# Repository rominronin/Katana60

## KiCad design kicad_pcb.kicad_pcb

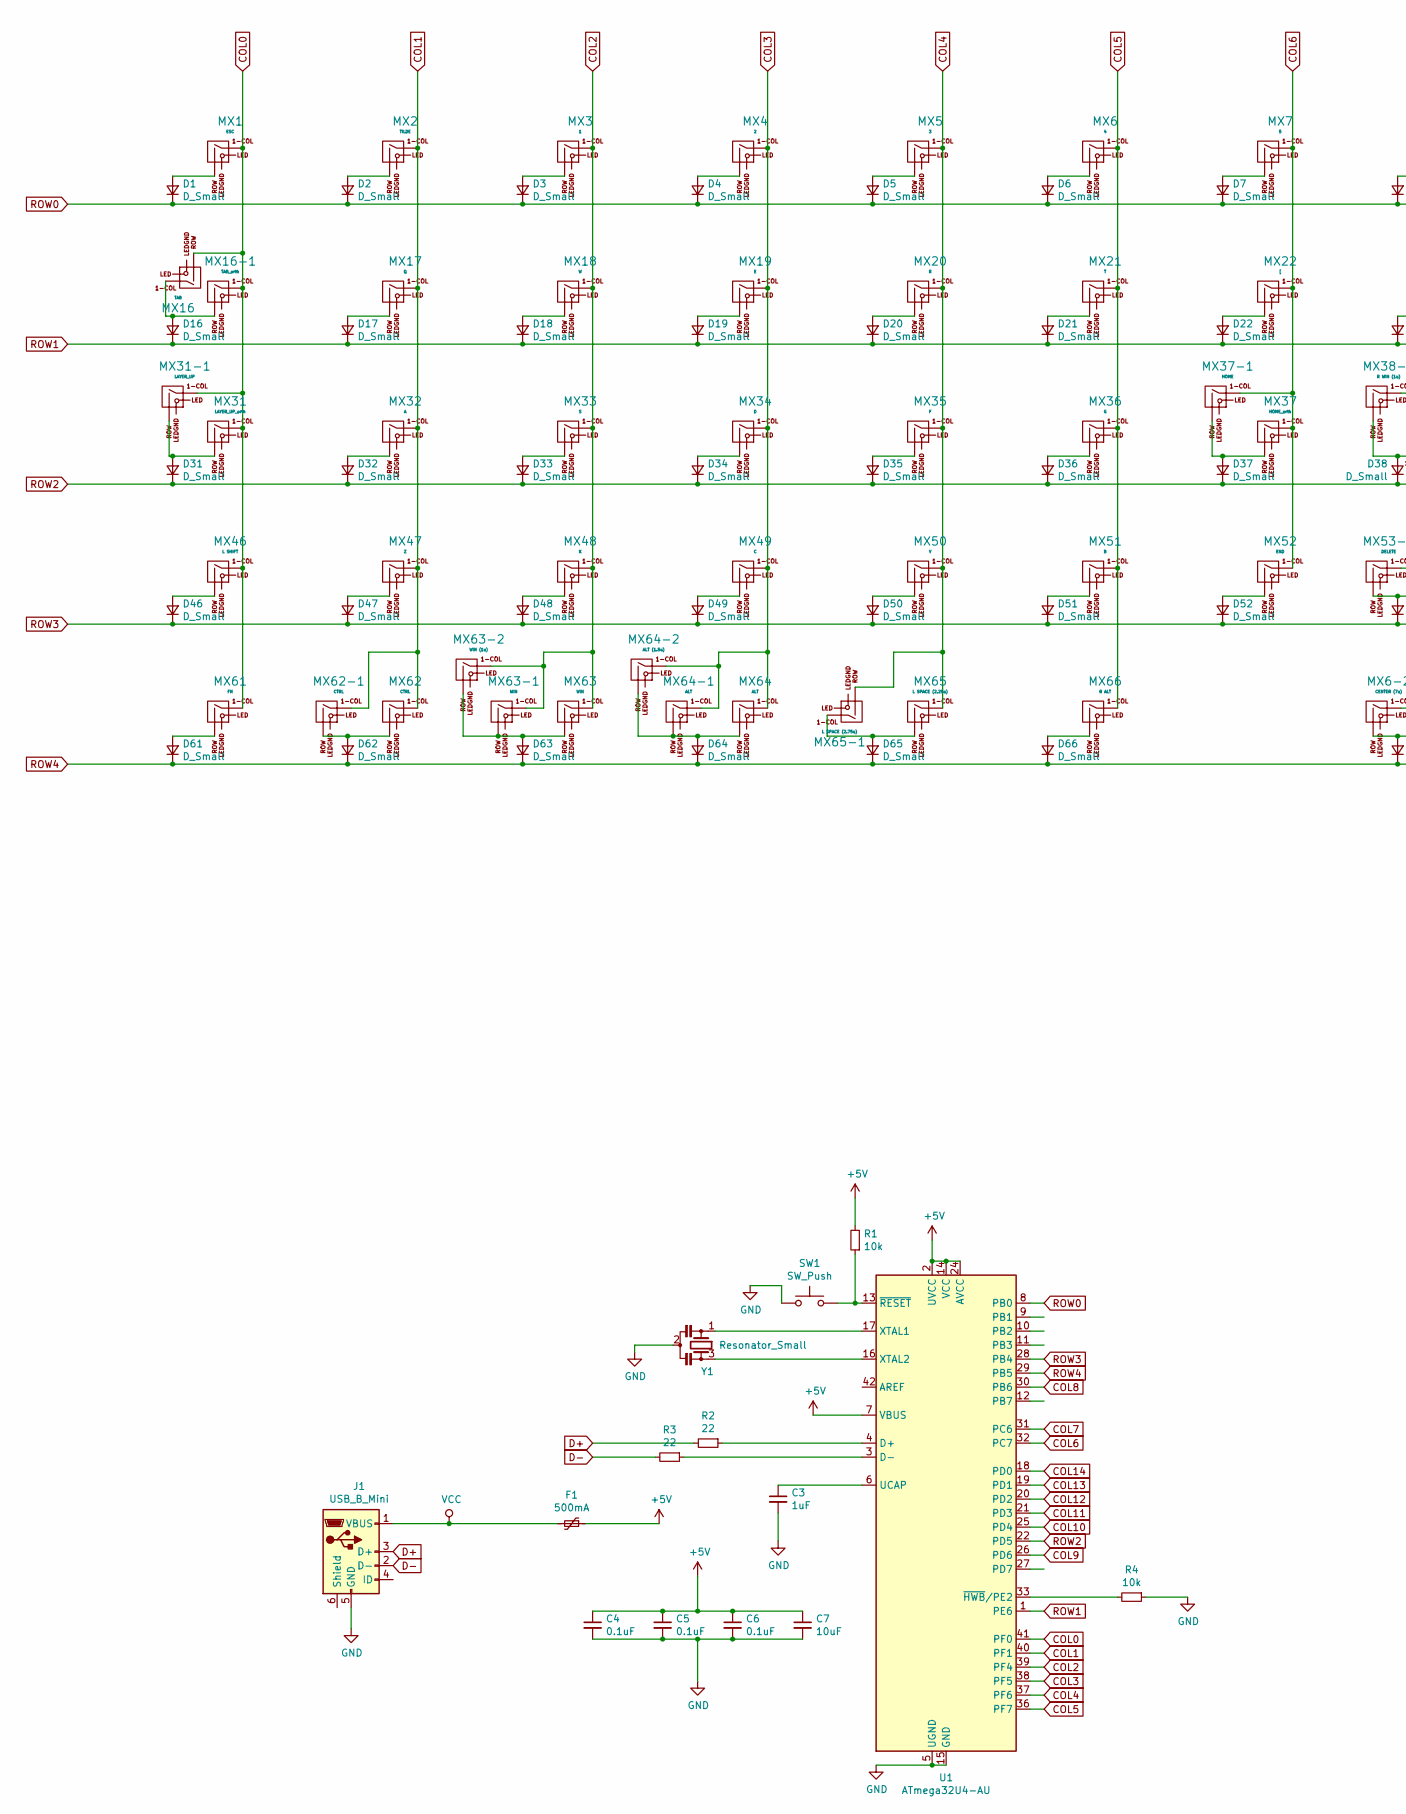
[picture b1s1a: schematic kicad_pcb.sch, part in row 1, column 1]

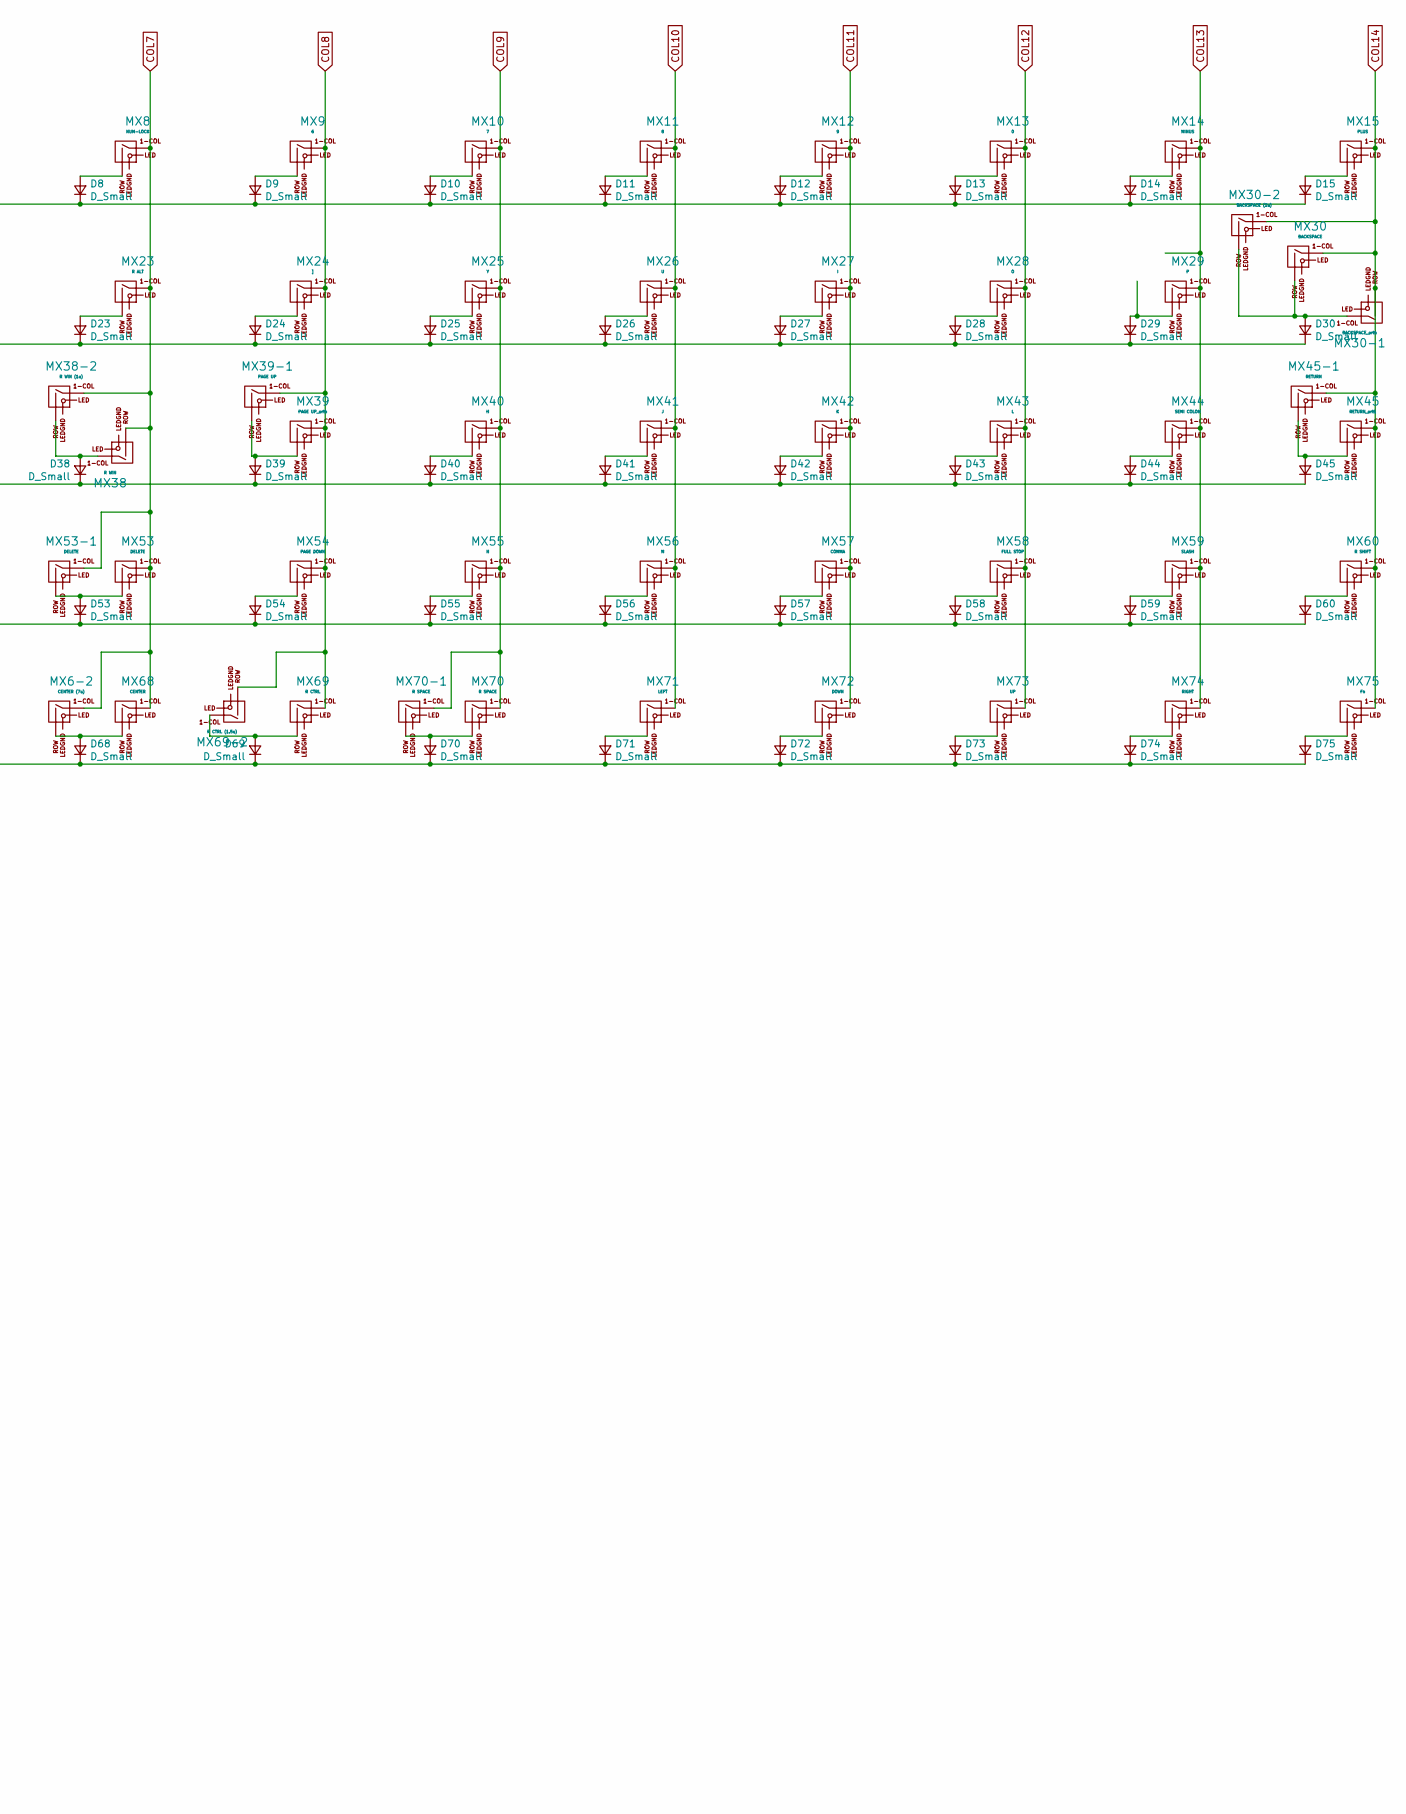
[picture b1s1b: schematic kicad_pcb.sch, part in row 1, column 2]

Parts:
C3: 1uF; C_0805_2012Metric
C4, C5, C6: 0.1uF; C_0805_2012Metric
C7: 10uF; D_0805_2012Metric
D1, D2, D3, D4, D5, D6, D7, D8, D9, D10, D11, D12, D13, D14, D15, D16, D17, D18, D19, D20, D21, D22, D23, D24, D25, D26, D27, D28, D29, D30, D31, D32, D33, D34, D35, D36, D37, D38, D39, D40, D41, D42, D43, D44, D45, D46, D47, D48, D49, D50, D51, D52, D53, D54, D55, D56, D57, D58, D59, D60, D61, D62, D63, D64, D65, D66, D68, D69, D70, D71, D72, D73, D74, D75: D_Small; D_0805_2012Metric
F1: 500mA; Fuse_1206_3216Metric
J1: USB_B_Mini; Molex-0548190519
MX1: ESC; MX-1U-NoLED
MX2: TILDE; MX-1U-NoLED
MX3: 1; MX-1U-NoLED
MX4: 2; MX-1U-NoLED
MX5: 3; MX-1U-NoLED
MX6: 4; MX-1U-NoLED
MX6-2: CENTER (7u); MX-7U-ReversedStabilizers-NoLED
MX7: 5; MX-1U-NoLED
MX8: NUM-LOCK; MX-1U-NoLED
MX9: 6; MX-1U-NoLED
MX10: 7; MX-1U-NoLED
MX11: 8; MX-1U-NoLED
MX12: 9; MX-1U-NoLED
MX13: 0; MX-1U-NoLED
MX14: MINUS; MX-1U-NoLED
MX15: PLUS; MX-1U-NoLED
MX16: TAB; MX-1.5U-NoLED
MX16-1: TAB_orth; MX-1U-NoLED
MX17: Q; MX-1U-NoLED
MX18: W; MX-1U-NoLED
MX19: E; MX-1U-NoLED
MX20: R; MX-1U-NoLED
MX21: T; MX-1U-NoLED
MX22: [; MX-1U-NoLED
MX23: R ALT; MX-2U-NoLED
MX24: ]; MX-1U-NoLED
MX25: Y; MX-1U-NoLED
MX26: U; MX-1U-NoLED
MX27: I; MX-1U-NoLED
MX28: O; MX-1U-NoLED
MX29: P; MX-1U-NoLED
MX30: BACKSPACE; MX-1.5U-NoLED
MX30-1: BACKSPACE_orth; MX-1U-NoLED
MX30-2: BACKSPACE (2u); MX-2U-NoLED
MX31: LAYER_UP_orth; MX-1U-NoLED
MX31-1: LAYER_UP; MX-1.25U-NoLED
MX32: A; MX-1U-NoLED
MX33: S; MX-1U-NoLED
MX34: D; MX-1U-NoLED
MX35: F; MX-1U-NoLED
MX36: G; MX-1U-NoLED
MX37: HOME_orth; MX-1U-NoLED
MX37-1: HOME; MX-1.25U-NoLED
MX38: R WIN; MX-1.25U-NoLED
MX38-2: R WIN (1u); MX-1U-NoLED
MX39: PAGE UP_orth; MX-1U-NoLED
MX39-1: PAGE UP; MX-1.25U-NoLED
MX40: H; MX-1U-NoLED
MX41: J; MX-1U-NoLED
MX42: K; MX-1U-NoLED
MX43: L; MX-1U-NoLED
MX44: SEMI COLON; MX-1U-NoLED
MX45: RETURN_orth; MX-1U-NoLED
MX45-1: RETURN; MX-1.25U-NoLED
MX46: L SHIFT; MX-1U-NoLED
MX47: Z; MX-1U-NoLED
MX48: X; MX-1U-NoLED
MX49: C; MX-1U-NoLED
MX50: V; MX-1U-NoLED
MX51: B; MX-1U-NoLED
MX52: END; MX-1U-NoLED
MX53: DELETE; MX-1U-NoLED
MX53-1: DELETE; MX-2.75U-ReversedStabilizers-NoLED
MX54: PAGE DOWN; MX-1U-NoLED
MX55: N; MX-1U-NoLED
MX56: M; MX-1U-NoLED
MX57: COMMA; MX-1U-NoLED
MX58: FULL STOP; MX-1U-NoLED
MX59: SLASH; MX-1U-NoLED
MX60: R SHIFT; MX-1U-NoLED
MX61: FN; MX-1U-NoLED
MX62: CTRL; MX-1.25U-NoLED
MX62-1: CTRL; MX-1.5U-NoLED
MX63, MX63-1: WIN; MX-1.25U-NoLED
MX63-2: WIN (1u); MX-1U-NoLED
MX64: ALT; MX-1.25U-NoLED
MX64-1: ALT; MX-1.5U-NoLED
MX64-2: ALT (1.5u); MX-1.5U-NoLED
MX65: L SPACE (2.25u); MX-2.25U-ReversedStabilizers-NoLED
MX65-1: L SPACE (2.75u); MX-2.75U-NoLED
MX66: R ALT; MX-1.5U-NoLED
MX68: CENTER; MX-1U-NoLED
MX69: R CTRL; MX-2.25U-NoLED
MX69-2: R CTRL (1.5u); MX-1.5U-NoLED
MX70: R SPACE; MX-2U-ReversedStabilizers-NoLED
MX70-1: R SPACE; MX-2.75U-NoLED
MX71: LEFT; MX-1U-NoLED
MX72: DOWN; MX-1U-NoLED
MX73: UP; MX-1U-NoLED
MX74: RIGHT; MX-1U-NoLED
MX75: Fn; MX-1U-NoLED
R1, R4: 10k; R_0805_2012Metric
R2, R3: 22; R_0805_2012Metric
SW1: SW_Push; SKQG-1155865
U1: ATmega32U4-AU; TQFP-44_10x10mm_P0.8mm
Y1: Resonator_Small; Resonator_SMD_muRata_CSTxExxV-3Pin_3.0x1.1mm

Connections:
+5V: C4.1, C5.1, C6.1, C7.1, F1.1, R1.2, U1.2 (UVCC), U1.7 (VBUS), U1.14 (VCC), U1.24 (AVCC), U1.34 (VCC), U1.44 (AVCC)
COL0: MX1.1 (COL), MX16.2 (ROW), MX16-1.1 (COL), MX31.1 (COL), MX31-1.1 (COL), MX46.1 (COL), MX61.1 (COL), U1.41 (PF0)
COL1: MX2.1 (COL), MX17.1 (COL), MX32.1 (COL), MX47.1 (COL), MX62.1 (COL), MX62-1.1 (COL), U1.40 (PF1)
COL2: MX3.1 (COL), MX18.1 (COL), MX33.1 (COL), MX48.1 (COL), MX63.1 (COL), MX63-1.1 (COL), MX63-2.1 (COL), U1.39 (PF4)
COL3: MX4.1 (COL), MX19.1 (COL), MX34.1 (COL), MX49.1 (COL), MX64.1 (COL), MX64-1.1 (COL), MX64-2.1 (COL), U1.38 (PF5)
COL4: MX5.1 (COL), MX20.1 (COL), MX35.1 (COL), MX50.1 (COL), MX65.1 (COL), MX65-1.2 (ROW), U1.37 (PF6)
COL5: MX6.1 (COL), MX21.1 (COL), MX36.1 (COL), MX51.1 (COL), MX66.1 (COL), U1.36 (PF7)
COL6: MX7.1 (COL), MX22.1 (COL), MX37.1 (COL), MX37-1.1 (COL), MX52.1 (COL), U1.32 (PC7)
COL7: MX6-2.1 (COL), MX8.1 (COL), MX23.1 (COL), MX38.2 (ROW), MX38-2.1 (COL), MX53.1 (COL), MX53-1.1 (COL), MX68.1 (COL), U1.31 (PC6)
COL8: MX9.1 (COL), MX24.1 (COL), MX39.1 (COL), MX39-1.1 (COL), MX54.1 (COL), MX69.1 (COL), MX69-2.2 (ROW), U1.30 (PB6)
COL9: MX10.1 (COL), MX25.1 (COL), MX40.1 (COL), MX55.1 (COL), MX70.1 (COL), MX70-1.1 (COL), U1.26 (PD6)
COL10: MX11.1 (COL), MX26.1 (COL), MX41.1 (COL), MX56.1 (COL), MX71.1 (COL), U1.25 (PD4)
COL11: MX12.1 (COL), MX27.1 (COL), MX42.1 (COL), MX57.1 (COL), MX72.1 (COL), U1.21 (PD3)
COL12: MX13.1 (COL), MX28.1 (COL), MX43.1 (COL), MX58.1 (COL), MX73.1 (COL), U1.20 (PD2)
COL13: MX14.1 (COL), MX29.1 (COL), MX44.1 (COL), MX59.1 (COL), MX74.1 (COL), U1.19 (PD1)
COL14: MX15.1 (COL), MX30.1 (COL), MX30-1.2 (ROW), MX30-2.1 (COL), MX45.1 (COL), MX45-1.1 (COL), MX60.1 (COL), MX75.1 (COL), U1.18 (PD0)
D+: J1.3 (D+), R2.2
D-: J1.2 (D-), R3.2
GND: C3.2, C4.2, C5.2, C6.2, C7.2, J1.5 (GND), R4.1, SW1.1, U1.5 (UGND), U1.15 (GND), U1.23 (GND), U1.35 (GND), U1.43 (GND), Y1.2
unnamed: C3.1, U1.6 (UCAP)
unnamed: D1.2 (A), MX1.2 (ROW)
unnamed: D2.2 (A), MX2.2 (ROW)
unnamed: D3.2 (A), MX3.2 (ROW)
unnamed: D4.2 (A), MX4.2 (ROW)
unnamed: D5.2 (A), MX5.2 (ROW)
unnamed: D6.2 (A), MX6.2 (ROW)
unnamed: D7.2 (A), MX7.2 (ROW)
unnamed: D8.2 (A), MX8.2 (ROW)
unnamed: D9.2 (A), MX9.2 (ROW)
unnamed: D10.2 (A), MX10.2 (ROW)
unnamed: D11.2 (A), MX11.2 (ROW)
unnamed: D12.2 (A), MX12.2 (ROW)
unnamed: D13.2 (A), MX13.2 (ROW)
unnamed: D14.2 (A), MX14.2 (ROW)
unnamed: D15.2 (A), MX15.2 (ROW)
unnamed: D16.2 (A), MX16.1 (COL), MX16-1.2 (ROW)
unnamed: D17.2 (A), MX17.2 (ROW)
unnamed: D18.2 (A), MX18.2 (ROW)
unnamed: D19.2 (A), MX19.2 (ROW)
unnamed: D20.2 (A), MX20.2 (ROW)
unnamed: D21.2 (A), MX21.2 (ROW)
unnamed: D22.2 (A), MX22.2 (ROW)
unnamed: D23.2 (A), MX23.2 (ROW)
unnamed: D24.2 (A), MX24.2 (ROW)
unnamed: D25.2 (A), MX25.2 (ROW)
unnamed: D26.2 (A), MX26.2 (ROW)
unnamed: D27.2 (A), MX27.2 (ROW)
unnamed: D28.2 (A), MX28.2 (ROW)
unnamed: D29.2 (A), MX29.2 (ROW)
unnamed: D30.2 (A), MX30.2 (ROW), MX30-1.1 (COL), MX30-2.2 (ROW)
unnamed: D31.2 (A), MX31.2 (ROW), MX31-1.2 (ROW)
unnamed: D32.2 (A), MX32.2 (ROW)
unnamed: D33.2 (A), MX33.2 (ROW)
unnamed: D34.2 (A), MX34.2 (ROW)
unnamed: D35.2 (A), MX35.2 (ROW)
unnamed: D36.2 (A), MX36.2 (ROW)
unnamed: D37.2 (A), MX37.2 (ROW), MX37-1.2 (ROW)
unnamed: D38.2 (A), MX38.1 (COL), MX38-2.2 (ROW)
unnamed: D39.2 (A), MX39.2 (ROW), MX39-1.2 (ROW)
unnamed: D40.2 (A), MX40.2 (ROW)
unnamed: D41.2 (A), MX41.2 (ROW)
unnamed: D42.2 (A), MX42.2 (ROW)
unnamed: D43.2 (A), MX43.2 (ROW)
unnamed: D44.2 (A), MX44.2 (ROW)
unnamed: D45.2 (A), MX45.2 (ROW), MX45-1.2 (ROW)
unnamed: D46.2 (A), MX46.2 (ROW)
unnamed: D47.2 (A), MX47.2 (ROW)
unnamed: D48.2 (A), MX48.2 (ROW)
unnamed: D49.2 (A), MX49.2 (ROW)
unnamed: D50.2 (A), MX50.2 (ROW)
unnamed: D51.2 (A), MX51.2 (ROW)
unnamed: D52.2 (A), MX52.2 (ROW)
unnamed: D53.2 (A), MX53.2 (ROW), MX53-1.2 (ROW)
unnamed: D54.2 (A), MX54.2 (ROW)
unnamed: D55.2 (A), MX55.2 (ROW)
unnamed: D56.2 (A), MX56.2 (ROW)
unnamed: D57.2 (A), MX57.2 (ROW)
unnamed: D58.2 (A), MX58.2 (ROW)
unnamed: D59.2 (A), MX59.2 (ROW)
unnamed: D60.2 (A), MX60.2 (ROW)
unnamed: D61.2 (A), MX61.2 (ROW)
unnamed: D62.2 (A), MX62.2 (ROW), MX62-1.2 (ROW)
unnamed: D63.2 (A), MX63.2 (ROW), MX63-1.2 (ROW), MX63-2.2 (ROW)
unnamed: D64.2 (A), MX64.2 (ROW), MX64-1.2 (ROW), MX64-2.2 (ROW)
unnamed: D65.2 (A), MX65.2 (ROW), MX65-1.1 (COL)
unnamed: D66.2 (A), MX66.2 (ROW)
unnamed: D68.2 (A), MX6-2.2 (ROW), MX68.2 (ROW)
unnamed: D69.2 (A), MX69.2 (ROW), MX69-2.1 (COL)
unnamed: D70.2 (A), MX70.2 (ROW), MX70-1.2 (ROW)
unnamed: D71.2 (A), MX71.2 (ROW)
unnamed: D72.2 (A), MX72.2 (ROW)
unnamed: D73.2 (A), MX73.2 (ROW)
unnamed: D74.2 (A), MX74.2 (ROW)
unnamed: D75.2 (A), MX75.2 (ROW)
unnamed: R1.1, SW1.2, U1.13 (~RESET)
unnamed: R2.1, U1.4 (D+)
unnamed: R3.1, U1.3 (D-)
unnamed: R4.2, U1.33 (~HWB~/PE2)
unnamed: U1.16 (XTAL2), Y1.3
unnamed: U1.17 (XTAL1), Y1.1
ROW0: D1.1 (K), D2.1 (K), D3.1 (K), D4.1 (K), D5.1 (K), D6.1 (K), D7.1 (K), D8.1 (K), D9.1 (K), D10.1 (K), D11.1 (K), D12.1 (K), D13.1 (K), D14.1 (K), D15.1 (K), U1.8 (PB0)
ROW1: D16.1 (K), D17.1 (K), D18.1 (K), D19.1 (K), D20.1 (K), D21.1 (K), D22.1 (K), D23.1 (K), D24.1 (K), D25.1 (K), D26.1 (K), D27.1 (K), D28.1 (K), D29.1 (K), D30.1 (K), U1.1 (PE6)
ROW2: D31.1 (K), D32.1 (K), D33.1 (K), D34.1 (K), D35.1 (K), D36.1 (K), D37.1 (K), D38.1 (K), D39.1 (K), D40.1 (K), D41.1 (K), D42.1 (K), D43.1 (K), D44.1 (K), D45.1 (K), U1.22 (PD5)
ROW3: D46.1 (K), D47.1 (K), D48.1 (K), D49.1 (K), D50.1 (K), D51.1 (K), D52.1 (K), D53.1 (K), D54.1 (K), D55.1 (K), D56.1 (K), D57.1 (K), D58.1 (K), D59.1 (K), D60.1 (K), U1.28 (PB4)
ROW4: D61.1 (K), D62.1 (K), D63.1 (K), D64.1 (K), D65.1 (K), D66.1 (K), D68.1 (K), D69.1 (K), D70.1 (K), D71.1 (K), D72.1 (K), D73.1 (K), D74.1 (K), D75.1 (K), U1.29 (PB5)
VCC: F1.2, J1.1 (VBUS)

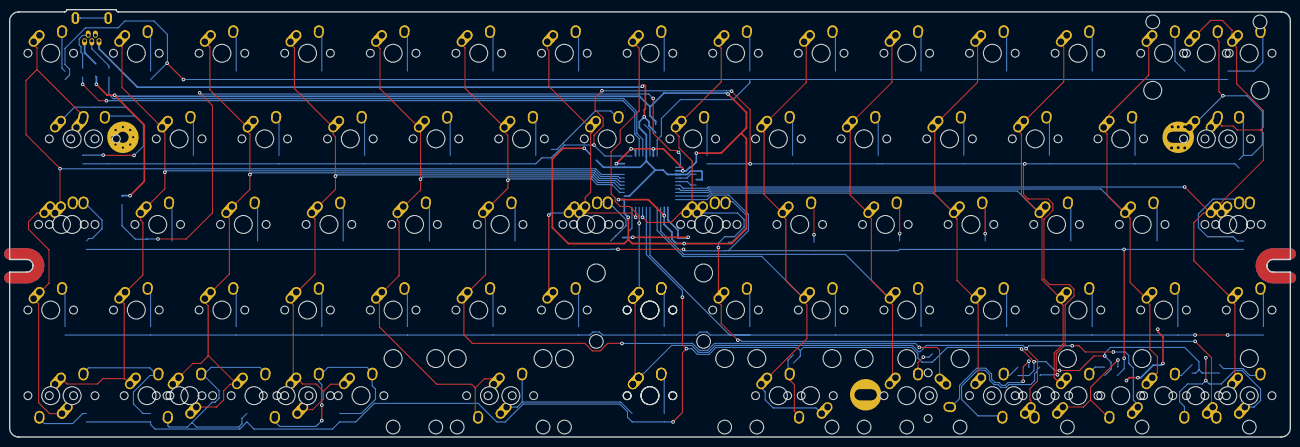
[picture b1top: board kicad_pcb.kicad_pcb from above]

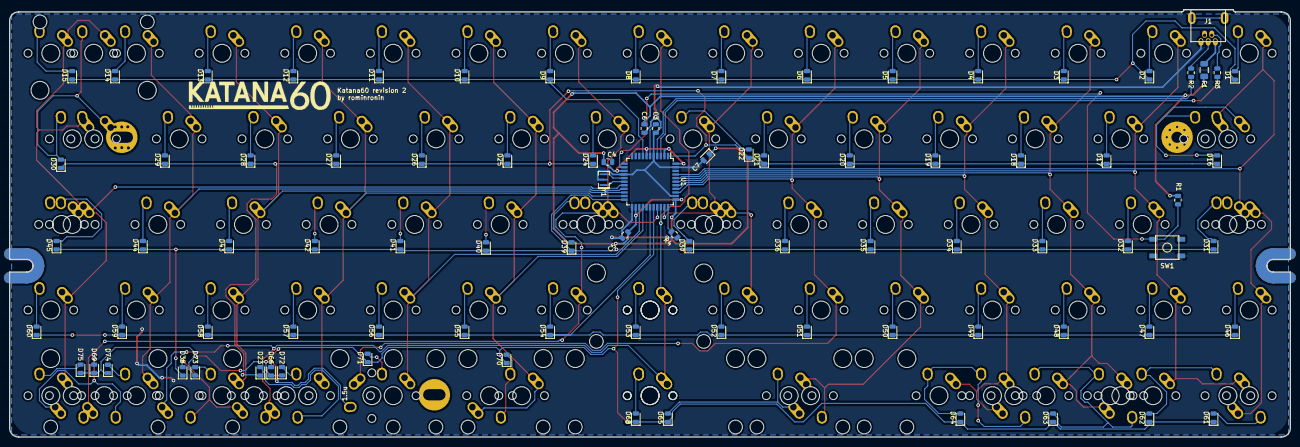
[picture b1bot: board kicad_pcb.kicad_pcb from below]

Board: 2 copper layers, 285.0 x 95.1 mm, 180 parts (88 on the bottom side), 106 nets.

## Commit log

2019-06-24 Ordered all keyboard rows
2019-06-24 Renamed all footprints except bottom row
2019-06-24 placed all the diodes
2019-07-02 updated the controller package
2019-07-02 latest changes
2019-07-02 flipped each component to the correct side, placed everything
2019-07-04 started with traces.
2019-07-04 further tracing
2019-07-05 further tracing applied
2019-07-06 first draft of the v2 PCB completed
2019-07-07 error-free first version
2019-07-07 ready to export
2019-07-07 updated the PCB outline footprint
2019-07-07 first export
2019-07-07 drill files added
2019-07-07 description
2019-07-07 updated the gerbers
2019-07-07 Added Katana60 logo to gerbers
2019-07-22 Gerber zip file
2019-07-26 ammended some incorrect footprints
2019-07-28 Moved and re-routed traces for C7 decoupling capacitor
2019-07-28 started to restructure the routing
2019-07-29 finished tracing repositioned componenets
2019-07-29 improved capacitor traces again
2019-07-29 made more improvements to the routing
2019-08-01 further routing
2019-08-01 refill all zones
2019-08-01 finished all routing, except the bottom row
2019-08-01 finished all traces
2019-08-10 adjustments to part labels
2019-08-11 rerouted the bottom row
2019-08-11 tidied up some overlapping pads
2019-08-11 Introduced mx and alps footprints for every switch
2019-08-11 Added symmetric 7u bottom row
2019-08-12 improved tracing
2019-08-12 created additional space around the stabilisers to prevent shorting
2019-08-13 disabled layers for easy visibility
2019-08-13 Gerber files ready for production
2019-08-14 updated the .gitignore file
2019-09-08 updated the usb footprint and tidied some traces
2019-09-08 Extended the GND plane.
2019-09-09 Rotated all diodes to a uniform direction.
2019-09-09 Improved diode labels
2019-10-01 final touches before exporting gerbers.
2019-10-01 updated the PCB text
2019-10-01 fixed a track to close to pad error
2019-10-01 ready for production gerber files.
2020-04-19 re-exported the USB footprint, repositioned it in the PCB file. Unlocked all parts
2020-04-19 last save before creating new gerbers
2020-04-19 re-exported the production files
